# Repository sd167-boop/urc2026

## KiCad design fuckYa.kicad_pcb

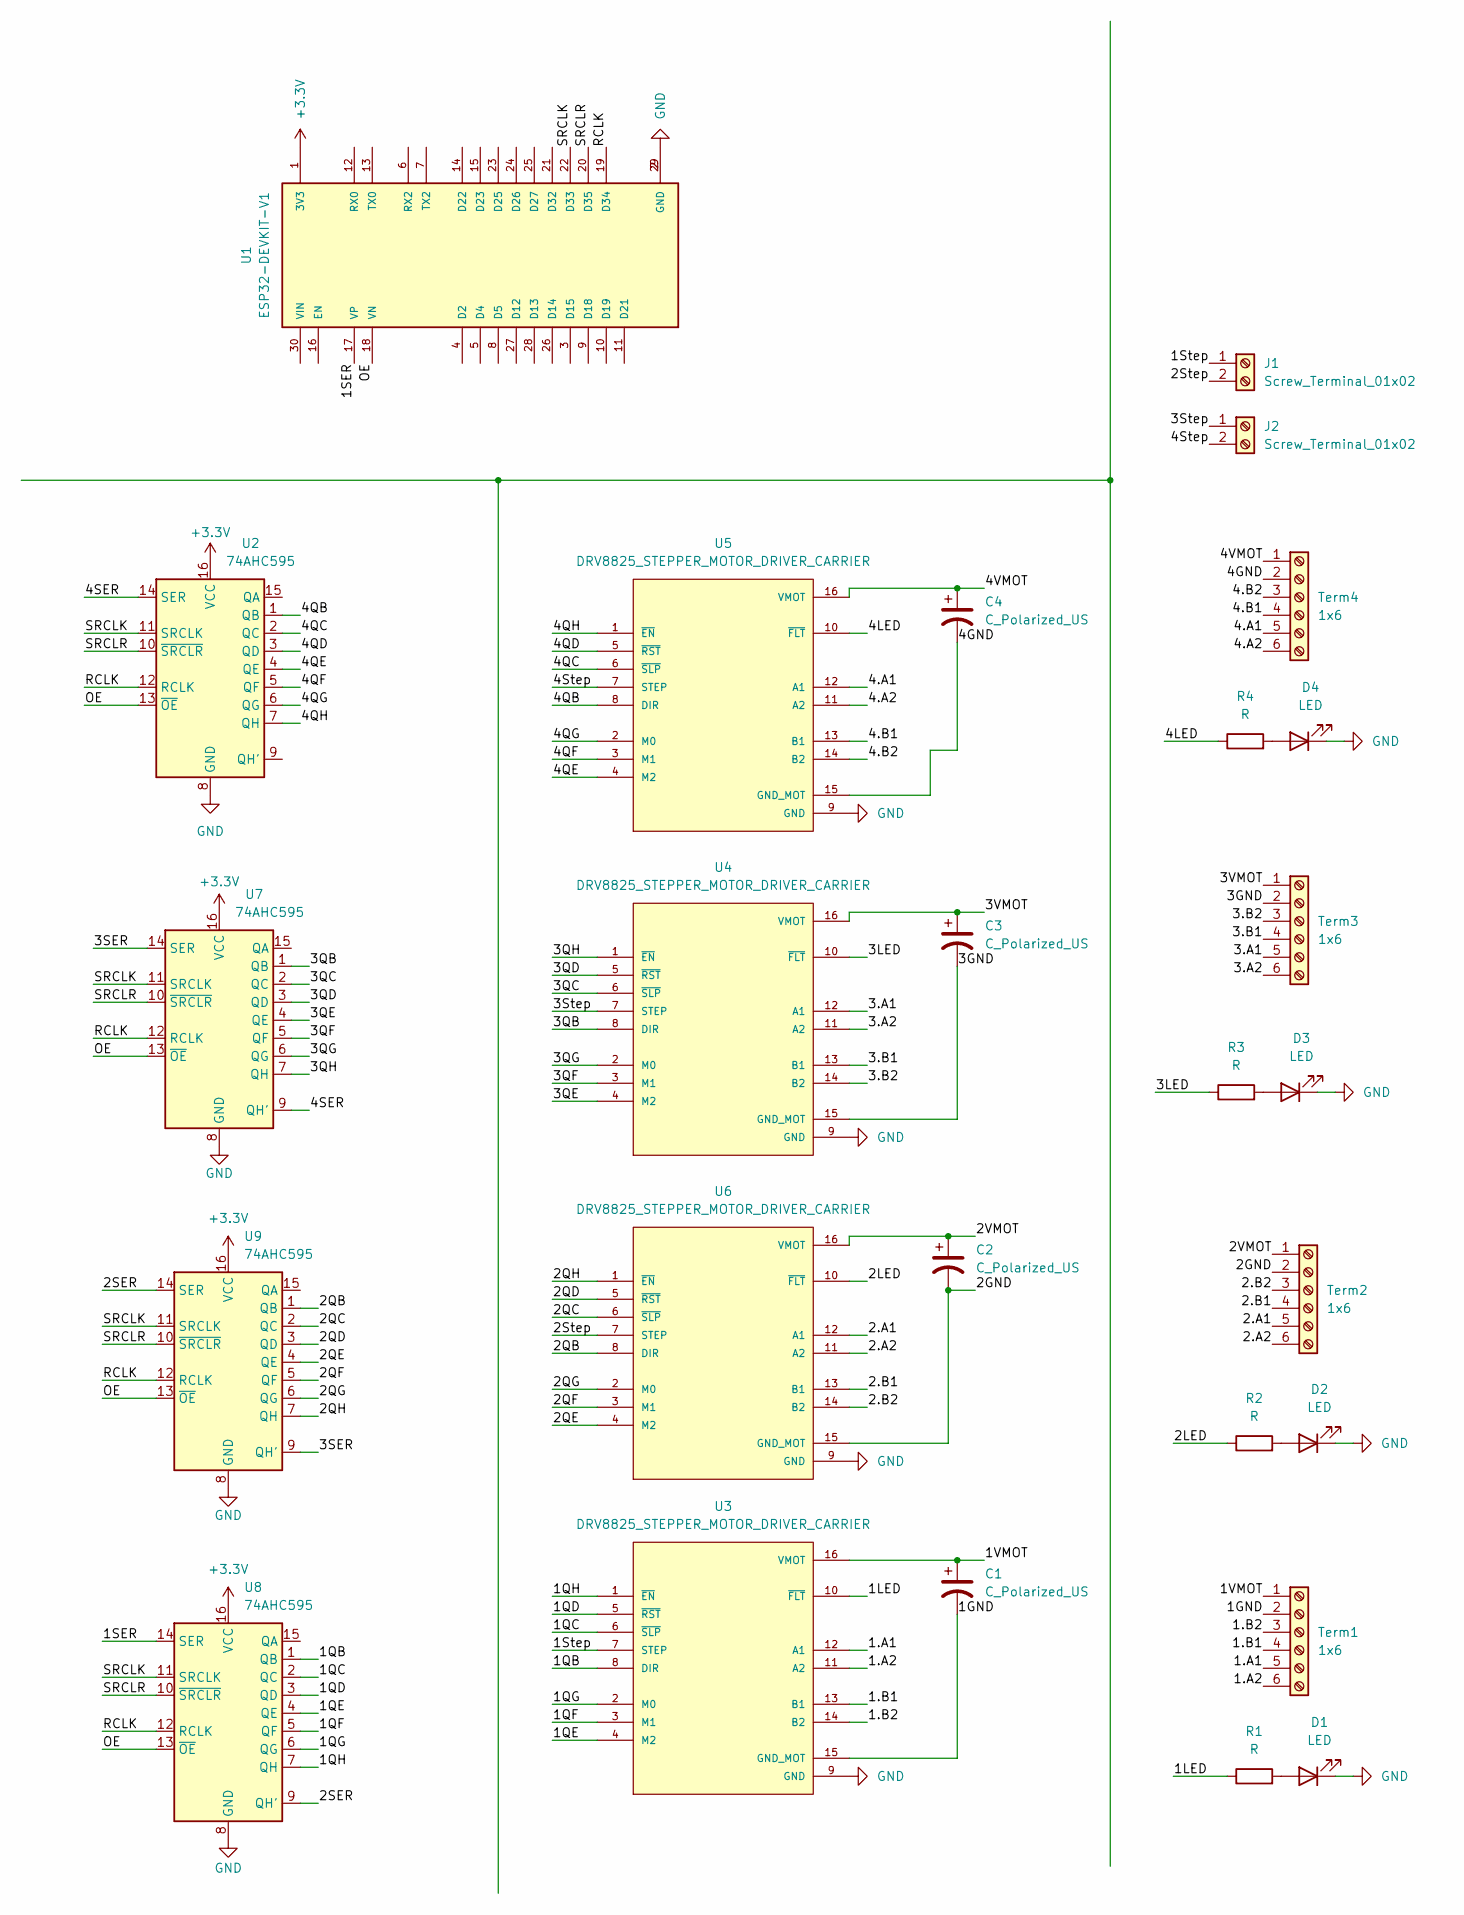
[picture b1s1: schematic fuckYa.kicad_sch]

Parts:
C1, C2, C3, C4: C_Polarized_US; CP_Radial_D5.0mm_P2.50mm
D1, D2, D3, D4: LED; LED_D3.0mm
J1, J2: Screw_Terminal_01x02; PhoenixContact_MCV_1,5_2-G-3.5_1x02_P3.50mm_Vertical
R1, R2, R3, R4: R; R_Axial_DIN0411_L9.9mm_D3.6mm_P12.70mm_Horizontal
Term1, Term2, Term3, Term4: 1x6; PhoenixContact_MCV_1,5_6-G-3.5_1x06_P3.50mm_Vertical
U1: ESP32-DEVKIT-V1; ESP32-C3-DevKitM-1; PARTREV N/A
U2, U7, U8, U9: 74AHC595; DIP794W45P254L1969H508Q16
U3, U4, U5, U6: DRV8825_STEPPER_MOTOR_DRIVER_CARRIER; IC_DRV8825_STEPPER_MOTOR_DRIVER_CARRIER

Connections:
+3.3V: U1.1 (3V3), U2.16 (VCC), U7.16 (VCC), U8.16 (VCC), U9.16 (VCC)
/1.A1: Term1.5, U3.12 (A1)
/1.A2: Term1.6, U3.11 (A2)
/1.B1: Term1.4, U3.13 (B1)
/1.B2: Term1.3, U3.14 (B2)
/1GND: C1.2, Term1.2, U3.15 (GND_MOT)
/1LED: R1.1, U3.10 (~FLT)
/1QB: U3.8 (DIR), U8.1 (QB)
/1QC: U3.6 (~SLP), U8.2 (QC)
/1QD: U3.5 (~RST), U8.3 (QD)
/1QE: U3.4 (M2), U8.4 (QE)
/1QF: U3.3 (M1), U8.5 (QF)
/1QG: U3.2 (M0), U8.6 (QG)
/1QH: U3.1 (~EN), U8.7 (QH)
/1SER: U1.17 (VP), U8.14 (SER)
/1Step: J1.1, U3.7 (STEP)
/1VMOT: C1.1, Term1.1, U3.16 (VMOT)
/2.A1: Term2.5, U6.12 (A1)
/2.A2: Term2.6, U6.11 (A2)
/2.B1: Term2.4, U6.13 (B1)
/2.B2: Term2.3, U6.14 (B2)
/2GND: C2.2, Term2.2, U6.15 (GND_MOT)
/2LED: R2.1, U6.10 (~FLT)
/2QB: U6.8 (DIR), U9.1 (QB)
/2QC: U6.6 (~SLP), U9.2 (QC)
/2QD: U6.5 (~RST), U9.3 (QD)
/2QE: U6.4 (M2), U9.4 (QE)
/2QF: U6.3 (M1), U9.5 (QF)
/2QG: U6.2 (M0), U9.6 (QG)
/2QH: U6.1 (~EN), U9.7 (QH)
/2SER: U8.9 (QH'), U9.14 (SER)
/2Step: J1.2, U6.7 (STEP)
/2VMOT: C2.1, Term2.1, U6.16 (VMOT)
/3.A1: Term3.5, U4.12 (A1)
/3.A2: Term3.6, U4.11 (A2)
/3.B1: Term3.4, U4.13 (B1)
/3.B2: Term3.3, U4.14 (B2)
/3GND: C3.2, Term3.2, U4.15 (GND_MOT)
/3LED: R3.1, U4.10 (~FLT)
/3QB: U4.8 (DIR), U7.1 (QB)
/3QC: U4.6 (~SLP), U7.2 (QC)
/3QD: U4.5 (~RST), U7.3 (QD)
/3QE: U4.4 (M2), U7.4 (QE)
/3QF: U4.3 (M1), U7.5 (QF)
/3QG: U4.2 (M0), U7.6 (QG)
/3QH: U4.1 (~EN), U7.7 (QH)
/3SER: U7.14 (SER), U9.9 (QH')
/3Step: J2.1, U4.7 (STEP)
/3VMOT: C3.1, Term3.1, U4.16 (VMOT)
/4.A1: Term4.5, U5.12 (A1)
/4.A2: Term4.6, U5.11 (A2)
/4.B1: Term4.4, U5.13 (B1)
/4.B2: Term4.3, U5.14 (B2)
/4GND: C4.2, Term4.2, U5.15 (GND_MOT)
/4LED: R4.1, U5.10 (~FLT)
/4QB: U2.1 (QB), U5.8 (DIR)
/4QC: U2.2 (QC), U5.6 (~SLP)
/4QD: U2.3 (QD), U5.5 (~RST)
/4QE: U2.4 (QE), U5.4 (M2)
/4QF: U2.5 (QF), U5.3 (M1)
/4QG: U2.6 (QG), U5.2 (M0)
/4QH: U2.7 (QH), U5.1 (~EN)
/4SER: U2.14 (SER), U7.9 (QH')
/4Step: J2.2, U5.7 (STEP)
/4VMOT: C4.1, Term4.1, U5.16 (VMOT)
/OE: U1.18 (VN), U2.13 (~OE), U7.13 (~OE), U8.13 (~OE), U9.13 (~OE)
/RCLK: U1.19 (D34), U2.12 (RCLK), U7.12 (RCLK), U8.12 (RCLK), U9.12 (RCLK)
/SRCLK: U1.22 (D33), U2.11 (SRCLK), U7.11 (SRCLK), U8.11 (SRCLK), U9.11 (SRCLK)
/SRCLR: U1.20 (D35), U2.10 (~SRCLR), U7.10 (~SRCLR), U8.10 (~SRCLR), U9.10 (~SRCLR)
GND: D1.1 (K), D2.1 (K), D3.1 (K), D4.1 (K), U1.2 (GND), U1.29 (GND), U2.8 (GND), U3.9 (GND), U4.9 (GND), U5.9 (GND), U6.9 (GND), U7.8 (GND), U8.8 (GND), U9.8 (GND)
unnamed: D1.2 (A), R1.2
unnamed: D2.2 (A), R2.2
unnamed: D3.2 (A), R3.2
unnamed: D4.2 (A), R4.2

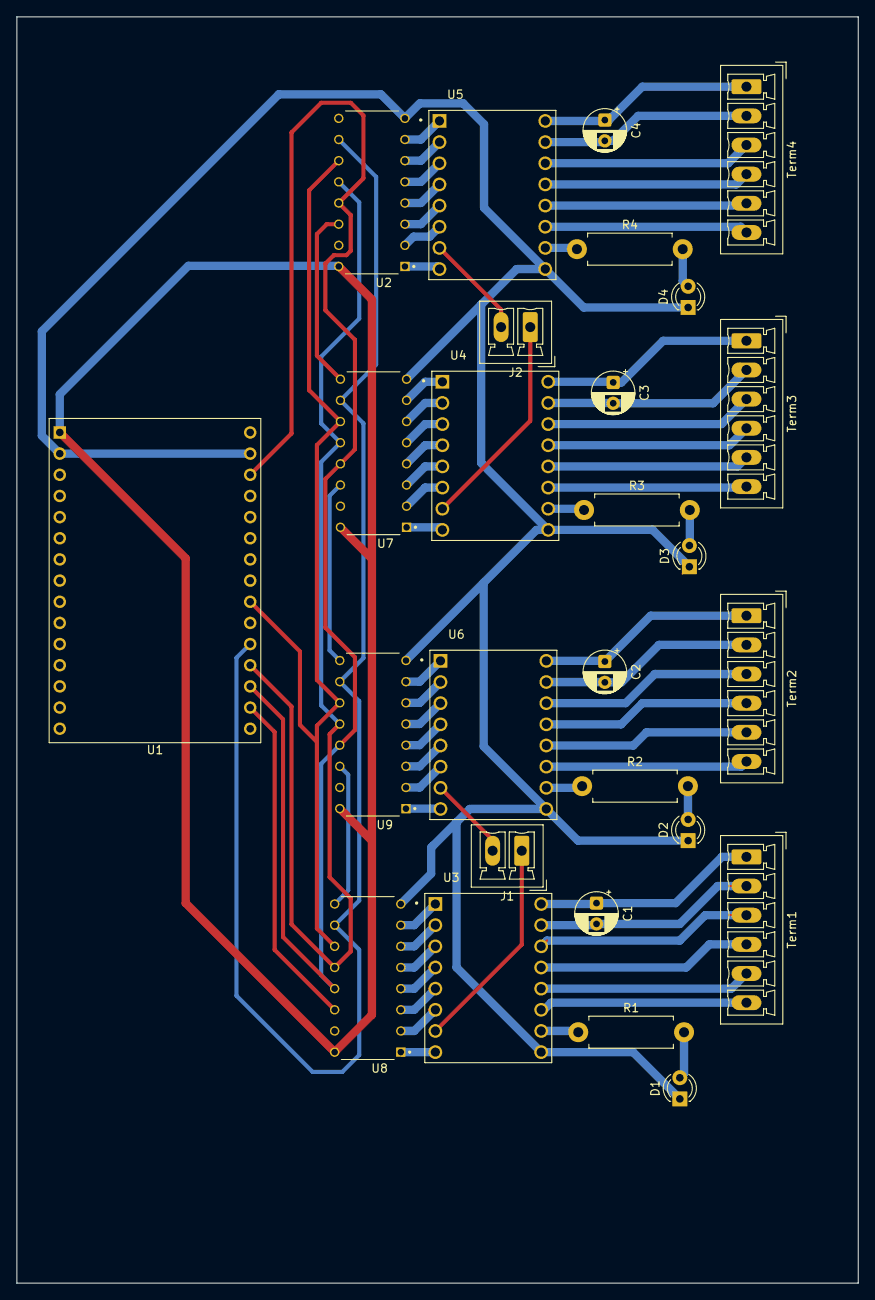
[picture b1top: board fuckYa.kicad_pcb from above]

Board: 2 copper layers, 101.0 x 152.0 mm, 27 parts (0 on the bottom side), 74 nets.
